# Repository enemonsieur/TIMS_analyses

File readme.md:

# TIMS Workspace Entry Point

This repository contains TIMS/TMS-EEG analysis code, experiment notes, and results across multiple experiments. This README is the navigation entry point for the workspace. It tells you where to start and where each kind of work lives. It is not the full scientific record.

## Workflow First

Use the repo in this order:

1. Read the latest memo chain to understand the current decision context.
2. Check the shared documentation files for memo, script, and figure rules.
3. Reuse the shared helper modules before adding logic to analysis scripts.
4. Open the main analyses when you need the scripts behind current conclusions.
5. Open exploratory analyses only when you are tracing probes, failed paths, or method tests.
6. Find outputs by experiment at the top level whenever possible.

## Latest Memo Chain

Memos in this repo are chained decision documents. Each new memo is expected to link the latest relevant earlier memo in its `Latest Shared Information` section, so the right reading order is newest to older, not oldest to newest. The current latest visible chain happens to be exp05, but that should not be assumed to stay true as the repo changes.

- Latest decision memo: [`MEMO_exp05_5_3_ctbs_intensity_decision.md`](/mnt/c/Users/njeuk/OneDrive/Documents/Charite%20Berlin/TIMS/docs/memos/MEMO_exp05_5_3_ctbs_intensity_decision.md)
- Immediate predecessor: [`MEMO_exp05_5_2_ctbs_recovery.md`](/mnt/c/Users/njeuk/OneDrive/Documents/Charite%20Berlin/TIMS/docs/memos/MEMO_exp05_5_2_ctbs_recovery.md)
- Earlier anchor in the same chain: [`MEMO_exp05_analysis.md`](/mnt/c/Users/njeuk/OneDrive/Documents/Charite%20Berlin/TIMS/docs/memos/MEMO_exp05_analysis.md)
- Memo rules/template: [`MEMO.md`](/mnt/c/Users/njeuk/OneDrive/Documents/Charite%20Berlin/TIMS/docs/memos/MEMO.md)

## How To Navigate TIMS

### Docs And Decision Records

- [`docs/memos/MEMO.md`](/mnt/c/Users/njeuk/OneDrive/Documents/Charite%20Berlin/TIMS/docs/memos/MEMO.md): memo template and chaining rules
- [`docs/standards/DATAVIZ_FRAMEWORK.md`](/mnt/c/Users/njeuk/OneDrive/Documents/Charite%20Berlin/TIMS/docs/standards/DATAVIZ_FRAMEWORK.md): figure planning and claim-first plotting rules
- [`docs/standards/SKRIPT.md`](/mnt/c/Users/njeuk/OneDrive/Documents/Charite%20Berlin/TIMS/docs/standards/SKRIPT.md): analysis script rules
- [`docs/standards/ANSWER.md`](/mnt/c/Users/njeuk/OneDrive/Documents/Charite%20Berlin/TIMS/docs/standards/ANSWER.md): response style guide for coding work
- [`docs/reference/TIMS_pilot_pipeline_map.md`](/mnt/c/Users/njeuk/OneDrive/Documents/Charite%20Berlin/TIMS/docs/reference/TIMS_pilot_pipeline_map.md): I/O-oriented pipeline map for the pilot/dose-response work
- [`docs/experiments/exp05.md`](/mnt/c/Users/njeuk/OneDrive/Documents/Charite%20Berlin/TIMS/docs/experiments/exp05.md): experiment-specific lab-book style reference for exp05

### Helper/Core Files

Shared reusable logic belongs in the core modules, not in new one-off scripts.

- [`preprocessing.py`](/mnt/c/Users/njeuk/OneDrive/Documents/Charite%20Berlin/TIMS/preprocessing.py): reusable preprocessing, epoching, timing, and metric helpers
- [`plot_helpers.py`](/mnt/c/Users/njeuk/OneDrive/Documents/Charite%20Berlin/TIMS/plot_helpers.py): reusable figure and plotting helpers

If logic is reused across analyses, it should be moved into one of these files instead of being copied into experiment scripts.

### Main Analyses

Main analyses are the scripts that support current conclusions or memo-backed outputs.

- [`main_analysis_exp03.py`](/mnt/c/Users/njeuk/OneDrive/Documents/Charite%20Berlin/TIMS/main_analysis_exp03.py)
- [`postclean_denoise_validate_exp03.py`](/mnt/c/Users/njeuk/OneDrive/Documents/Charite%20Berlin/TIMS/postclean_denoise_validate_exp03.py)
- [`compare_stim_baseline_exp03.py`](/mnt/c/Users/njeuk/OneDrive/Documents/Charite%20Berlin/TIMS/compare_stim_baseline_exp03.py)
- [`analyses_TEP_exp04.py`](/mnt/c/Users/njeuk/OneDrive/Documents/Charite%20Berlin/TIMS/analyses_TEP_exp04.py)
- [`analyses_spectral_exp04.py`](/mnt/c/Users/njeuk/OneDrive/Documents/Charite%20Berlin/TIMS/analyses_spectral_exp04.py)
- [`analyses_dynamics_exp04.py`](/mnt/c/Users/njeuk/OneDrive/Documents/Charite%20Berlin/TIMS/analyses_dynamics_exp04.py)
- [`analyses_artifact_exp05.py`](/mnt/c/Users/njeuk/OneDrive/Documents/Charite%20Berlin/TIMS/analyses_artifact_exp05.py)
- [`analyses_ssd_exp05.py`](/mnt/c/Users/njeuk/OneDrive/Documents/Charite%20Berlin/TIMS/analyses_ssd_exp05.py)

### Exploratory Analyses

Exploratory analyses are probes, method experiments, drafts, and non-decision-driving checks. They are useful for development and evidence, but they should not be treated as the default scientific entry point.

- [`analyses_ssd_exp05_skript.py`](/mnt/c/Users/njeuk/OneDrive/Documents/Charite%20Berlin/TIMS/analyses_ssd_exp05_skript.py)
- [`explore_exp05_fc1_baseline_ssd.py`](/mnt/c/Users/njeuk/OneDrive/Documents/Charite%20Berlin/TIMS/explore_exp05_fc1_baseline_ssd.py)
- [`analyses_ica_topo_exp05.py`](/mnt/c/Users/njeuk/OneDrive/Documents/Charite%20Berlin/TIMS/analyses_ica_topo_exp05.py)
- [`compare_baseline_gt_exp05.py`](/mnt/c/Users/njeuk/OneDrive/Documents/Charite%20Berlin/TIMS/compare_baseline_gt_exp05.py)
- [`analyze_baseline_gt.py`](/mnt/c/Users/njeuk/OneDrive/Documents/Charite%20Berlin/TIMS/analyze_baseline_gt.py)
- [`plot_channels_epoch_avg_exp05.py`](/mnt/c/Users/njeuk/OneDrive/Documents/Charite%20Berlin/TIMS/plot_channels_epoch_avg_exp05.py)
- [`evidence`](/mnt/c/Users/njeuk/OneDrive/Documents/Charite%20Berlin/TIMS/evidence): comparison runs, probes, and failure evidence
- [`old`](/mnt/c/Users/njeuk/OneDrive/Documents/Charite%20Berlin/TIMS/old): archived analyses and older experiment work

## Where Things Live

### Raw Data

- [`TIMS_data_sync`](/mnt/c/Users/njeuk/OneDrive/Documents/Charite%20Berlin/TIMS/TIMS_data_sync): BrainVision recordings and related synced data

### Protocol Files

- Top-level `.tims` and protocol `.py` files define programmable stimulation protocols used by specific experiments

### Main Results

Experiment outputs should be easy to find from the top level by experiment name.

- `exp03` outputs:
  - [`exp03_pulse_centered_analysis_run03`](/mnt/c/Users/njeuk/OneDrive/Documents/Charite%20Berlin/TIMS/exp03_pulse_centered_analysis_run03)
  - [`exp03_postpulse_fixed_channels`](/mnt/c/Users/njeuk/OneDrive/Documents/Charite%20Berlin/TIMS/exp03_postpulse_fixed_channels)
- `exp04` outputs:
  - [`EXP04_TEP_analysis`](/mnt/c/Users/njeuk/OneDrive/Documents/Charite%20Berlin/TIMS/EXP04_TEP_analysis)
  - [`EXP04_spectral_analysis`](/mnt/c/Users/njeuk/OneDrive/Documents/Charite%20Berlin/TIMS/EXP04_spectral_analysis)
  - [`EXP04_dynamics_analysis`](/mnt/c/Users/njeuk/OneDrive/Documents/Charite%20Berlin/TIMS/EXP04_dynamics_analysis)
- `exp05` outputs:
  - [`EXP05_artifact_characterization`](/mnt/c/Users/njeuk/OneDrive/Documents/Charite%20Berlin/TIMS/EXP05_artifact_characterization)
  - [`EXP05_baseline_gt_analysis`](/mnt/c/Users/njeuk/OneDrive/Documents/Charite%20Berlin/TIMS/EXP05_baseline_gt_analysis)
  - [`EXP05_baseline_comparison`](/mnt/c/Users/njeuk/OneDrive/Documents/Charite%20Berlin/TIMS/EXP05_baseline_comparison)
  - [`EXP05_channel_avg`](/mnt/c/Users/njeuk/OneDrive/Documents/Charite%20Berlin/TIMS/EXP05_channel_avg)
  - [`EXP05_explore_fc1_baseline_ssd`](/mnt/c/Users/njeuk/OneDrive/Documents/Charite%20Berlin/TIMS/EXP05_explore_fc1_baseline_ssd)
  - [`EXP05_ica_30pct`](/mnt/c/Users/njeuk/OneDrive/Documents/Charite%20Berlin/TIMS/EXP05_ica_30pct)
  - [`EXP05_ssd_recovery`](/mnt/c/Users/njeuk/OneDrive/Documents/Charite%20Berlin/TIMS/EXP05_ssd_recovery)
  - [`EXP05_ssd_recovery_skript`](/mnt/c/Users/njeuk/OneDrive/Documents/Charite%20Berlin/TIMS/EXP05_ssd_recovery_skript)
- `exp06` outputs:
  - [`EXP06_qc_context`](/mnt/c/Users/njeuk/OneDrive/Documents/Charite%20Berlin/TIMS/EXP06_qc_context)

### Exploratory Or Legacy Results

- [`evidence`](/mnt/c/Users/njeuk/OneDrive/Documents/Charite%20Berlin/TIMS/evidence): probe outputs and comparison artifacts
- [`old`](/mnt/c/Users/njeuk/OneDrive/Documents/Charite%20Berlin/TIMS/old): archived or legacy material that is no longer in the active result layout

## Classification Rules

- Main analyses: scripts that directly support current conclusions, memo-backed figures, or decision documents
- Exploratory analyses: probes, method tests, drafts, and diagnostics that help development but are not the default basis for conclusions
- Results: organize by experiment at the top level where possible, and avoid deep nested result trees unless there is a clear need

## Current Layout Issues

The repo now uses top-level experiment result folders more consistently, but there are still cleanup edges to resolve over time. The remaining direction is to keep new outputs experiment-scoped at the top level, avoid loose result files in the repo root, and keep exploratory material clearly separated from main result folders.

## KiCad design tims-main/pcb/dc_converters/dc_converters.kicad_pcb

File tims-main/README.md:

# tims
Design files for a Temporal Interference Magnetic Stimulator (TIMS)

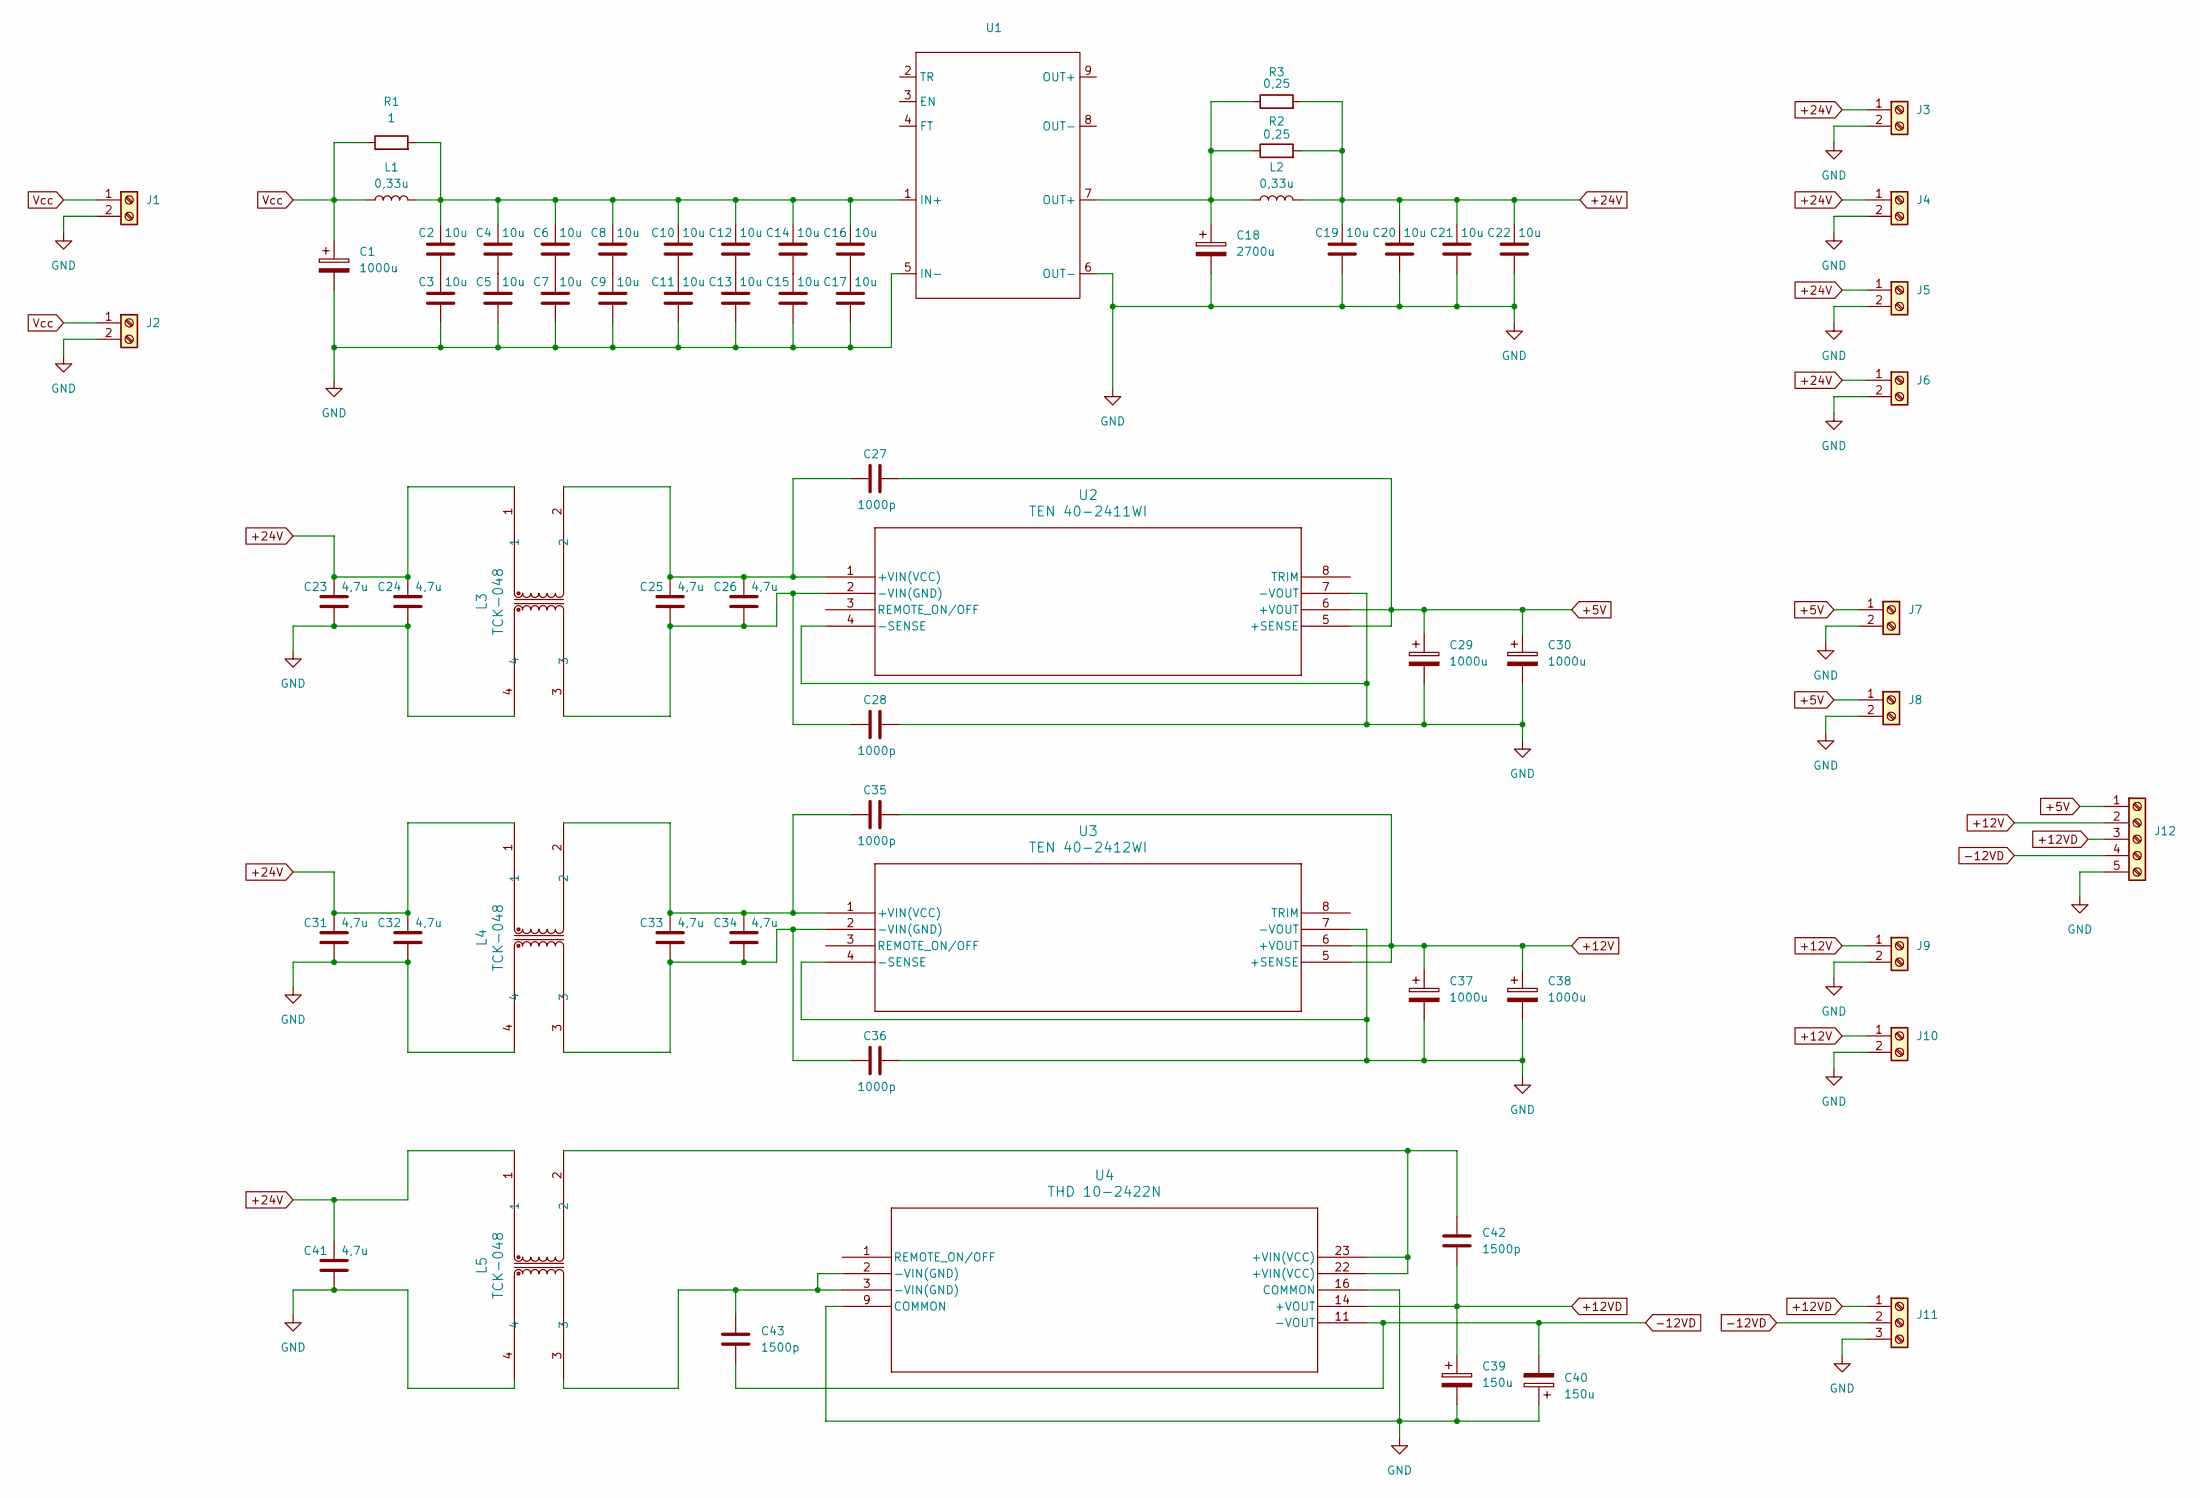
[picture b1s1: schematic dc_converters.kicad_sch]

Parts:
C1: 1000u; CP_Radial_D30.0mm_P10.00mm_SnapIn
C2, C3, C4, C5, C6, C7, C8, C9, C10, C11, C12, C13, C14, C15, C16, C17, C19, C20, C21, C22: 10u; C_1210_3225Metric
C18: 2700u; CP_Radial_D18.0mm_P7.50mm
C23, C24, C25, C26, C31, C32, C33, C34, C41: 4,7u; C_1206_3216Metric
C27, C28, C35, C36: 1000p; C_1206_3216Metric
C29, C30, C37, C38: 1000u; CP_Radial_D12.5mm_P5.00mm
C39, C40: 150u; CP_Radial_D10.0mm_P5.00mm
C42, C43: 1500p; C_1206_3216Metric
J1, J2, J3, J4, J5, J6, J7, J8, J9, J10: TerminalBlock_Phoenix_PT-1,5-2-5.0-H_1x02_P5.00mm_Horizontal
J11: TerminalBlock_Phoenix_PT-1,5-3-5.0-H_1x03_P5.00mm_Horizontal
J12: TerminalBlock_Phoenix_PT-1,5-5-5.0-H_1x05_P5.00mm_Horizontal
L1, L2: 0,33u; L_Wuerth_HCM-1390
L3, L4, L5: TCK-048; IND_TCK-048_TRP
R1: 1; R_1206_3216Metric
R2, R3: 0,25; R_2512_6332Metric
U1: DCM3623TA5N26B4T00
U2: TEN 40-2411WI; TEN 40WI_TRP
U3: TEN 40-2412WI; TEN 40WI_TRP
U4: THD 10-2422N; THD 10N DUAL_TRP

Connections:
+5V: C27.2, C29.1, C30.1, J7.1, J8.1, J12.1, U2.5 (+SENSE), U2.6 (+VOUT)
+12V: C35.2, C37.1, C38.1, J9.1, J10.1, J12.2, U3.5 (+SENSE), U3.6 (+VOUT)
+12VD: C39.1, C42.2, J11.1, J12.3, U4.14 (+VOUT)
+24V: C19.1, C20.1, C21.1, C22.1, C23.1, C24.1, C31.1, C32.1, C41.1, J3.1, J4.1, J5.1, J6.1, L2.2, L3.1, L4.1, L5.1, R2.2, R3.2
-12VD: C40.2, C43.2, J11.2, J12.4, U4.11 (-VOUT)
GND: C1.2, C3.2, C5.2, C7.2, C9.2, C11.2, C13.2, C15.2, C17.2, C18.2, C19.2, C20.2, C21.2, C22.2, C23.2, C24.2, C28.2, C29.2, C30.2, C31.2, C32.2, C36.2, C37.2, C38.2, C39.2, C40.1, C41.2, J1.2, J2.2, J3.2, J4.2, J5.2, J6.2, J7.2, J8.2, J9.2, J10.2, J11.3, J12.5, L3.4, L4.4, L5.4, U1.5 (IN-), U1.6 (OUT-), U2.4 (-SENSE), U2.7 (-VOUT), U3.4 (-SENSE), U3.7 (-VOUT), U4.9 (COMMON), U4.16 (COMMON)
unnamed: C2.2, C3.1
unnamed: C4.2, C5.1
unnamed: C6.2, C7.1
unnamed: C8.2, C9.1
unnamed: C10.2, C11.1
unnamed: C12.2, C13.1
unnamed: C14.2, C15.1
unnamed: C16.2, C17.1
unnamed: C18.1, L2.1, R2.1, R3.1, U1.7 (OUT+)
unnamed: C42.1, L5.2, U4.22 (+VIN(VCC)), U4.23 (+VIN(VCC))
unnamed: C43.1, L5.3, U4.2 (-VIN(GND)), U4.3 (-VIN(GND))
unnamed: C2.1, C4.1, C6.1, C8.1, C10.1, C12.1, C14.1, C16.1, L1.2, R1.2, U1.1 (IN+)
unnamed: C25.1, C26.1, C27.1, L3.2, U2.1 (+VIN(VCC))
unnamed: C25.2, C26.2, C28.1, L3.3, U2.2 (-VIN(GND))
unnamed: C33.1, C34.1, C35.1, L4.2, U3.1 (+VIN(VCC))
unnamed: C33.2, C34.2, C36.1, L4.3, U3.2 (-VIN(GND))
Vcc: C1.1, J1.1, J2.1, L1.1, R1.1

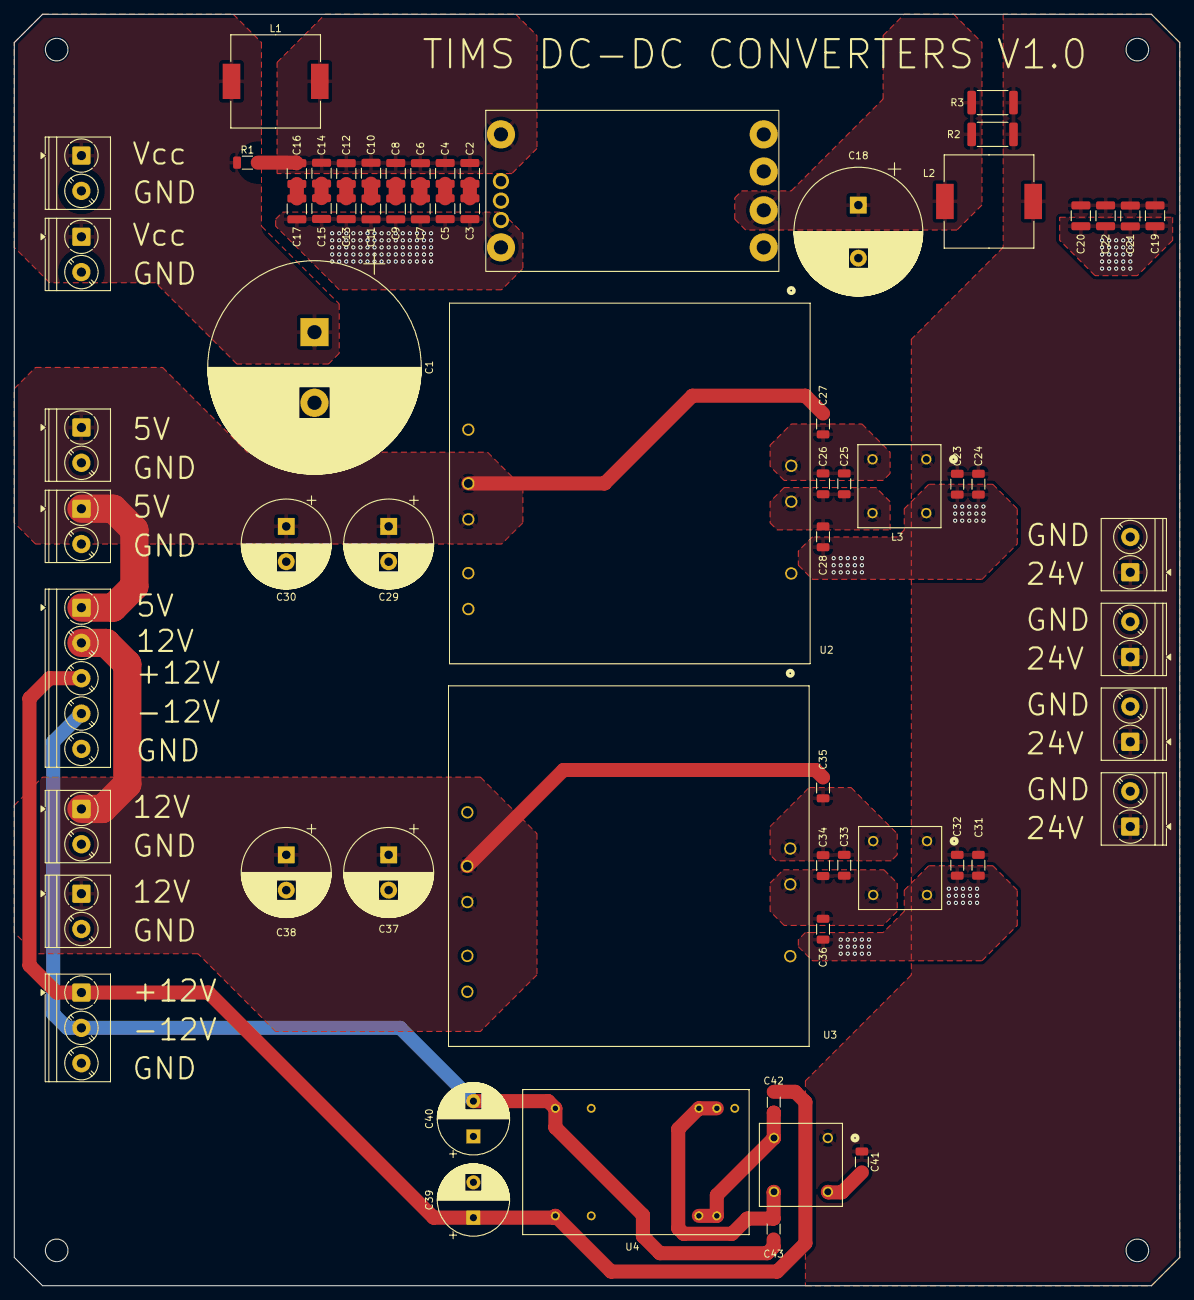
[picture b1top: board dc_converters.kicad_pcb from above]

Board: 2 copper layers, 165.0 x 180.0 mm, 67 parts (0 on the bottom side), 23 nets.

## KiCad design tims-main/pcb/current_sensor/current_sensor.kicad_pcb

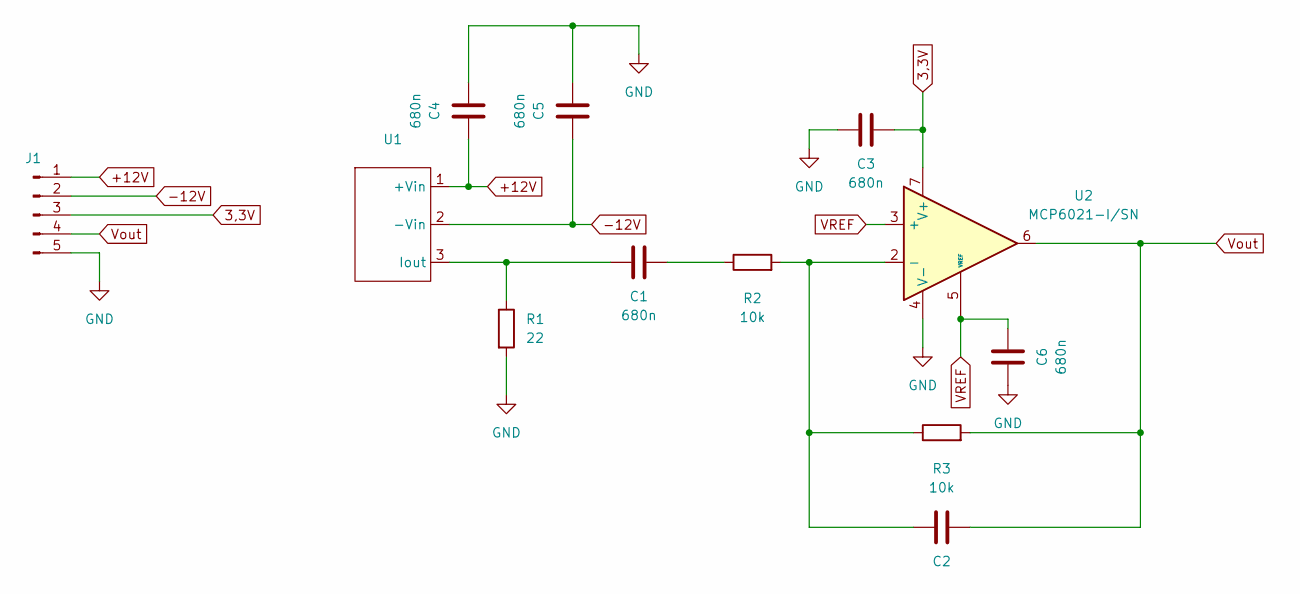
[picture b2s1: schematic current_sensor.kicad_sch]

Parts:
C1, C3, C4, C5, C6: 680n; C_1206_3216Metric
C2: C_1206_3216Metric
J1: Conn_01x05_Pin; JST_PH_B5B-PH-K_1x05_P2.00mm_Vertical
R1: 22; R_1206_3216Metric
R2, R3: 10k; R_1206_3216Metric
U1: CSNT651
U2: MCP6021-I/SN; SOIC-8_3.9x4.9mm_P1.27mm

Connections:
3,3V: C3.1, J1.3, U2.7 (V+)
+12V: C4.1, J1.1, U1.1 (+Vin)
-12V: C5.1, J1.2, U1.2 (-Vin)
GND: C3.2, C4.2, C5.2, C6.2, J1.5, R1.2, U2.4 (V-)
unnamed: C1.1, R2.1
unnamed: C1.2, R1.1, U1.3 (Iout)
unnamed: C2.2, R2.2, R3.1, U2.2 (-)
VREF: C6.1, U2.3 (+), U2.5 (VREF)
Vout: C2.1, J1.4, R3.2, U2.6

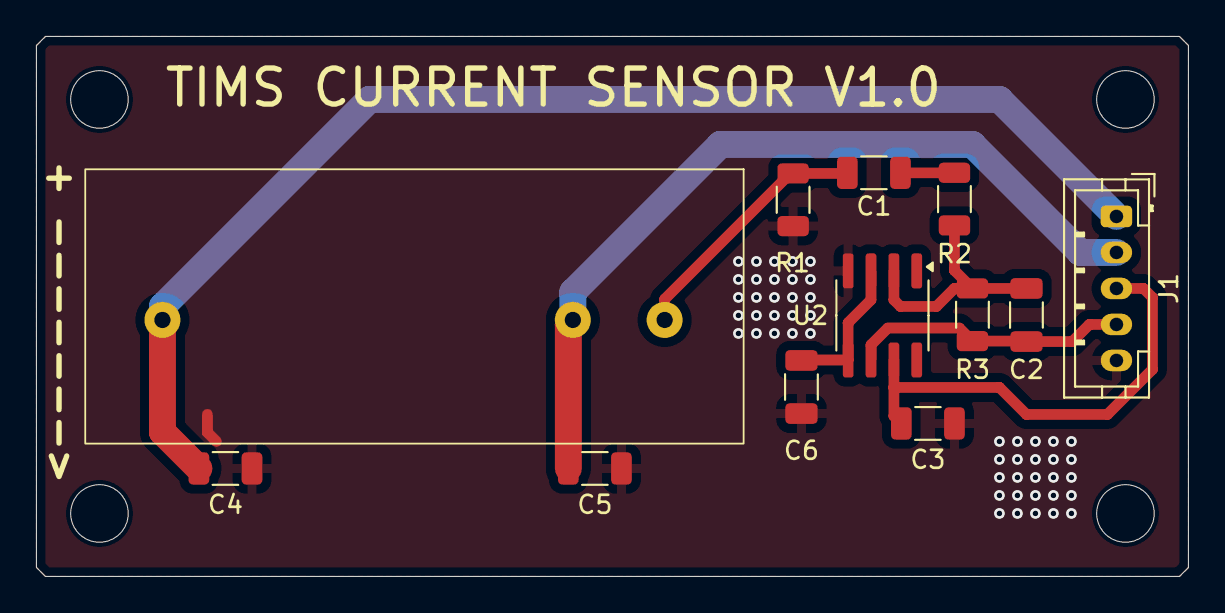
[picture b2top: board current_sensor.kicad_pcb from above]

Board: 2 copper layers, 64.0 x 30.0 mm, 12 parts (0 on the bottom side), 9 nets.

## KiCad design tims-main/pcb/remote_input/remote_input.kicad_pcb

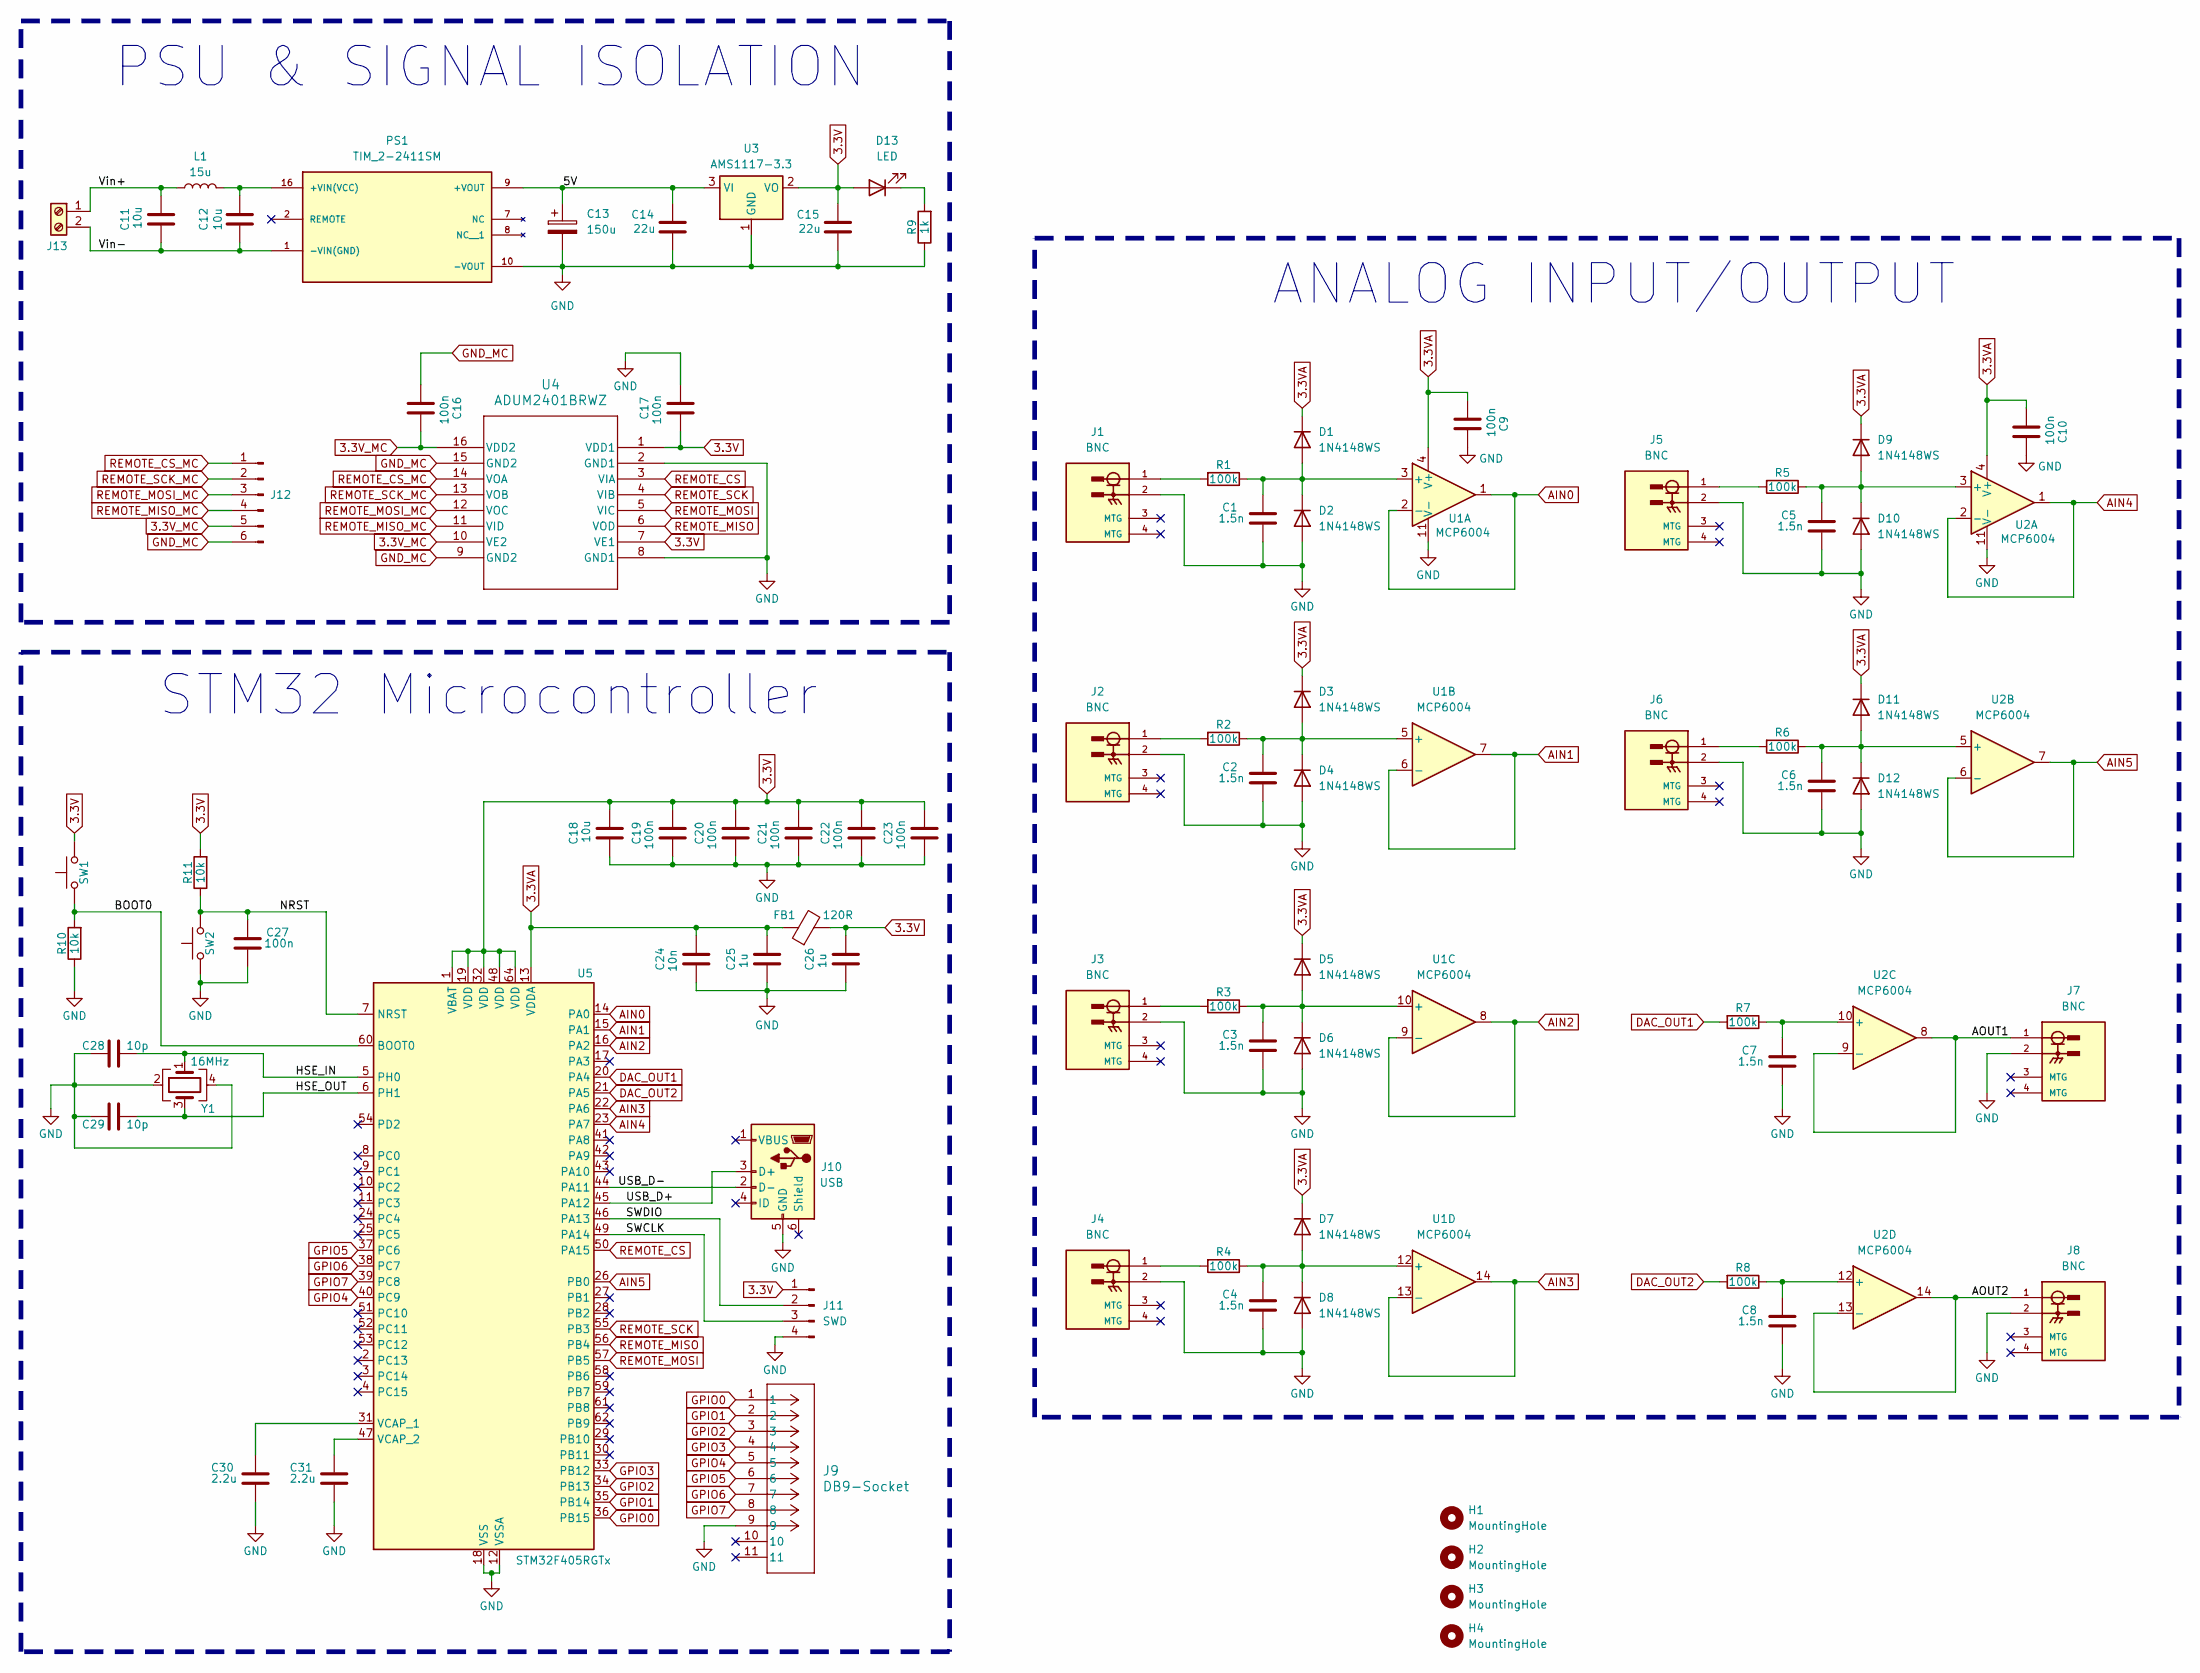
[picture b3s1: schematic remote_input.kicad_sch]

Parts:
C1, C2, C3, C4, C5, C6, C7, C8: 1.5n; C_1206_3216Metric
C9, C10, C16, C17, C19, C20, C21, C22, C23, C27: 100n; C_0402_1005Metric
C11, C12: 10u; C_1206_3216Metric
C13: 150u; CP_Radial_D10.0mm_P5.00mm
C14, C15: 22u; C_0805_2012Metric
C18: 10u; C_0603_1608Metric
C24: 10n; C_0402_1005Metric
C25, C26: 1u; C_0603_1608Metric
C28, C29: 10p; C_0402_1005Metric
C30, C31: 2.2u; C_0603_1608Metric
D1, D2, D3, D4, D5, D6, D7, D8, D9, D10, D11, D12: 1N4148WS; D_SOD-323
D13: LED; LED_0805_2012Metric
FB1: 120R; L_1206_3216Metric
H1, H2, H3, H4: MountingHole; MountingHole_3.2mm_M3
J1, J2, J3, J4, J5, J6, J7, J8: BNC; BNC-5227161-1; PARTREV B4
J9: DB9-Socket; DB9_SOCKET_2311765_TEC
J10: USB; USB_Micro-B_Wuerth_629105150521_WITH_3D
J11: SWD; PinHeader_1x04_P2.54mm_Vertical
J12: Conn_01x06_Pin; JST_PH_B6B-PH-K_1x06_P2.00mm_Vertical
J13: TerminalBlock_Phoenix_PT-1,5-2-5.0-H_1x02_P5.00mm_Horizontal
L1: 15u; IND_K-131_TRP
PS1: TIM_2-2411SM; CONV_TIM_2-2411SM; PARTREV August 20, 2020
R1, R2, R3, R4, R5, R6, R7, R8: 100k; R_1206_3216Metric
R9: 1k; R_1206_3216Metric
R10, R11: 10k; R_1206_3216Metric
SW1, SW2: SW_Push; SW-TS-1088-AR02016
U1, U2: MCP6004; SOIC-14_3.9x8.7mm_P1.27mm
U3: AMS1117-3.3; SOT-223-3_TabPin2
U4: ADUM2401BRWZ; SOIC-16W_7.5x10.3mm_P1.27mm
U5: STM32F405RGTx; LQFP-64_10x10mm_P0.5mm
Y1: 16MHz; Crystal_SMD_3225-4Pin_3.2x2.5mm

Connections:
3.3V: C15.2, C17.1, C18.1, C19.2, C20.2, C21.2, C22.2, C23.2, C26.2, D13.2 (A), FB1.2, J11.1, R11.2, SW1.2, U3.2 (VO), U4.1 (VDD1), U4.7 (VE1), U5.1 (VBAT), U5.19 (VDD), U5.32 (VDD), U5.48 (VDD), U5.64 (VDD)
3.3VA: C9.1, C10.1, C24.2, C25.2, D1.1 (K), D3.1 (K), D5.1 (K), D7.1 (K), D9.1 (K), D11.1 (K), FB1.1, U1.4 (V+), U2.4 (V+), U5.13 (VDDA)
3.3V_MC: C16.1, J12.5, U4.10 (VE2), U4.16 (VDD2)
/5V: C13.1, C14.2, PS1.9 (+VOUT), U3.3 (VI)
/AOUT1: J7.1, U2.8, U2.9 (-)
/AOUT2: J8.1, U2.13 (-), U2.14
/BOOT0: R10.2, SW1.1, U5.60 (BOOT0)
/HSE_IN: C28.1, U5.5 (PH0), Y1.1
/HSE_OUT: C29.1, U5.6 (PH1), Y1.3
/NRST: C27.2, R11.1, SW2.2, U5.7 (NRST)
/SWCLK: J11.3, U5.49 (PA14)
/SWDIO: J11.2, U5.46 (PA13)
/USB_D+: J10.3 (D+), U5.45 (PA12)
/USB_D-: J10.2 (D-), U5.44 (PA11)
/Vin+: C11.1, J13.1, L1.1
/Vin-: C11.2, C12.2, J13.2, PS1.1 (-VIN(GND))
AIN0: U1.1, U1.2 (-), U5.14 (PA0)
AIN1: U1.6 (-), U1.7, U5.15 (PA1)
AIN2: U1.8, U1.9 (-), U5.16 (PA2)
AIN3: U1.13 (-), U1.14, U5.22 (PA6)
AIN4: U2.1, U2.2 (-), U5.23 (PA7)
AIN5: U2.6 (-), U2.7, U5.26 (PB0)
DAC_OUT1: R7.2, U5.20 (PA4)
DAC_OUT2: R8.2, U5.21 (PA5)
GND: C1.1, C2.1, C3.1, C4.1, C5.1, C6.1, C7.1, C8.1, C9.2, C10.2, C13.2, C14.1, C15.1, C17.2, C18.2, C19.1, C20.1, C21.1, C22.1, C23.1, C24.1, C25.1, C26.1, C27.1, C28.2, C29.2, C30.1, C31.1, D2.2 (A), D4.2 (A), D6.2 (A), D8.2 (A), D10.2 (A), D12.2 (A), J1.2, J2.2, J3.2, J4.2, J5.2, J6.2, J7.2, J8.2, J9.9, J10.5 (GND), J11.4, PS1.10 (-VOUT), R9.1, R10.1, SW2.1, U1.11 (V-), U2.11 (V-), U3.1 (GND), U4.2 (GND1), U4.8 (GND1), U5.12 (VSSA), U5.18 (VSS), U5.63 (VSS), Y1.2, Y1.4
GND_MC: C16.2, J12.6, U4.9 (GND2), U4.15 (GND2)
GPIO0: J9.1, U5.36 (PB15)
GPIO1: J9.2, U5.35 (PB14)
GPIO2: J9.3, U5.34 (PB13)
GPIO3: J9.4, U5.33 (PB12)
GPIO4: J9.5, U5.40 (PC9)
GPIO5: J9.6, U5.37 (PC6)
GPIO6: J9.7, U5.38 (PC7)
GPIO7: J9.8, U5.39 (PC8)
unnamed: C1.2, D1.2 (A), D2.1 (K), R1.1, U1.3 (+)
unnamed: C2.2, D3.2 (A), D4.1 (K), R2.1, U1.5 (+)
unnamed: C3.2, D5.2 (A), D6.1 (K), R3.1, U1.10 (+)
unnamed: C4.2, D7.2 (A), D8.1 (K), R4.1, U1.12 (+)
unnamed: C5.2, D9.2 (A), D10.1 (K), R5.1, U2.3 (+)
unnamed: C6.2, D11.2 (A), D12.1 (K), R6.1, U2.5 (+)
unnamed: D13.1 (K), R9.2
unnamed: J1.1, R1.2
unnamed: J2.1, R2.2
unnamed: J3.1, R3.2
unnamed: J4.1, R4.2
unnamed: J5.1, R5.2
unnamed: J6.1, R6.2
unnamed: C12.1, L1.2, PS1.16 (+VIN(VCC))
unnamed: C7.2, R7.1, U2.10 (+)
unnamed: C8.2, R8.1, U2.12 (+)
unnamed: C30.2, U5.31 (VCAP_1)
unnamed: C31.2, U5.47 (VCAP_2)
REMOTE_CS: U4.3 (VIA), U5.50 (PA15)
REMOTE_CS_MC: J12.1, U4.14 (VOA)
REMOTE_MISO: U4.6 (VOD), U5.56 (PB4)
REMOTE_MISO_MC: J12.4, U4.11 (VID)
REMOTE_MOSI: U4.5 (VIC), U5.57 (PB5)
REMOTE_MOSI_MC: J12.3, U4.12 (VOC)
REMOTE_SCK: U4.4 (VIB), U5.55 (PB3)
REMOTE_SCK_MC: J12.2, U4.13 (VOB)

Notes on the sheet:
PSU & SIGNAL ISOLATION
STM32 Microcontroller
ANALOG INPUT/OUTPUT

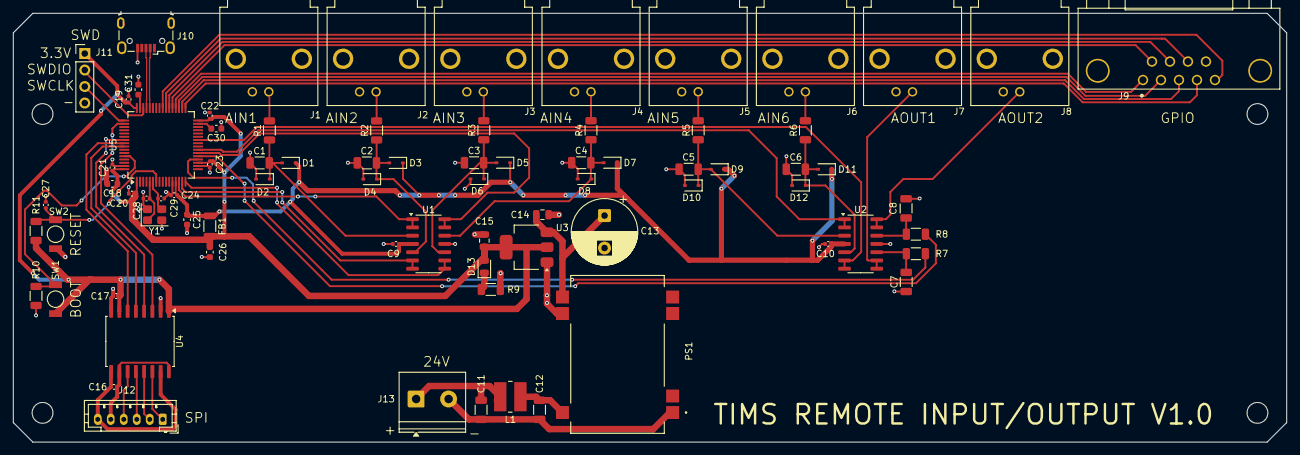
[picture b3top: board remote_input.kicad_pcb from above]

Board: 2 copper layers, 196.0 x 66.0 mm, 83 parts (0 on the bottom side), 60 nets.

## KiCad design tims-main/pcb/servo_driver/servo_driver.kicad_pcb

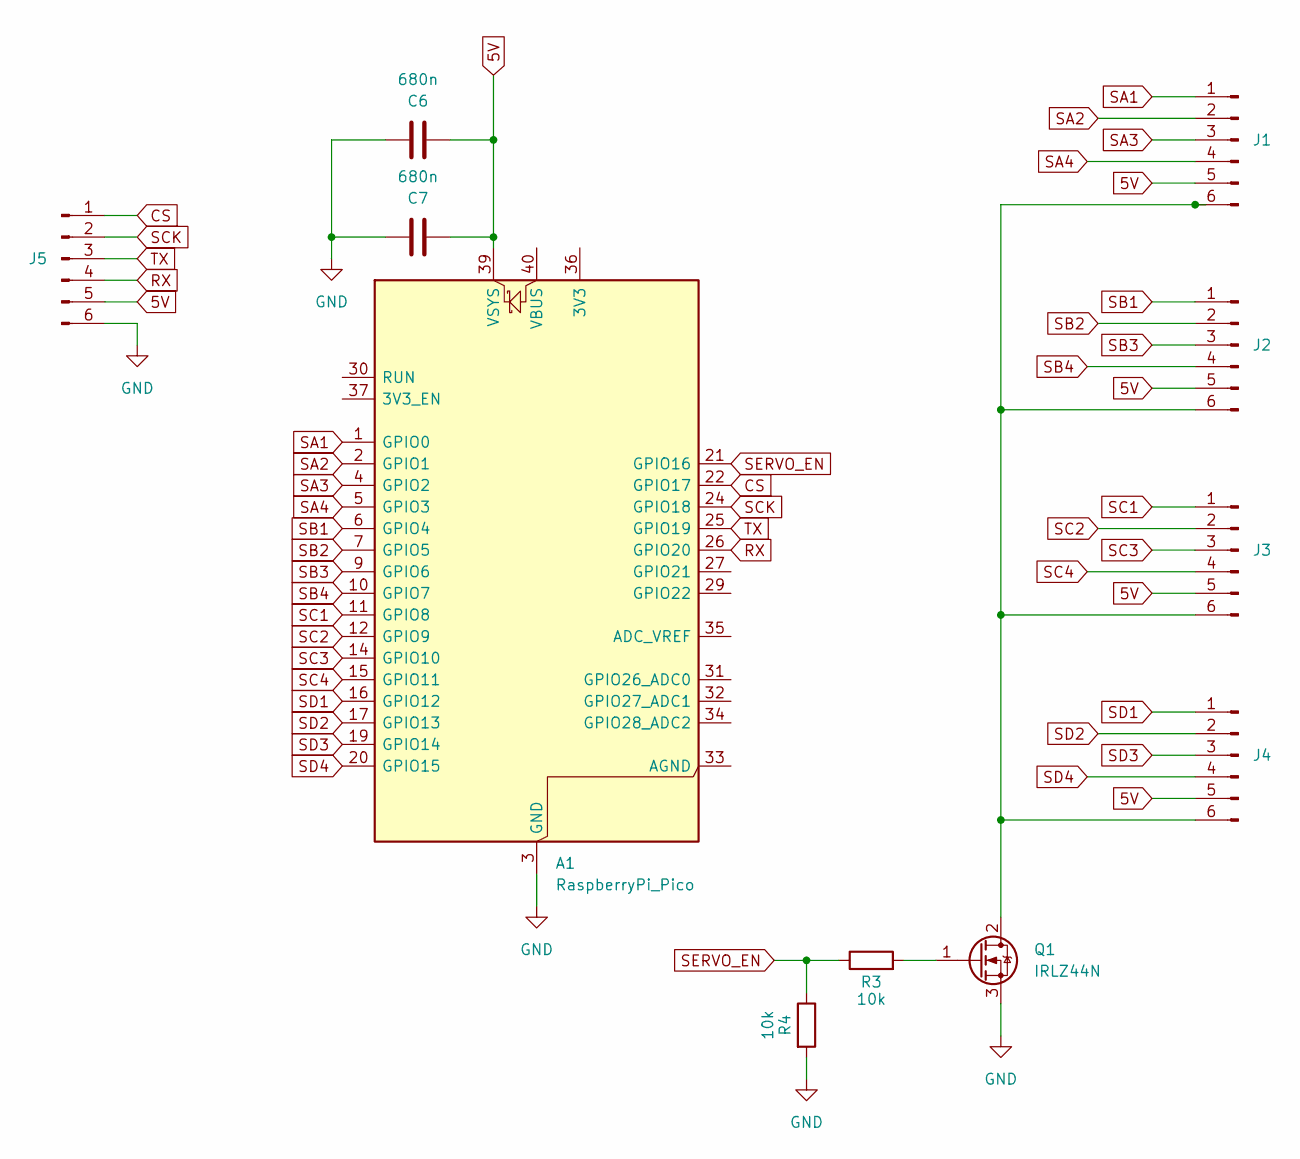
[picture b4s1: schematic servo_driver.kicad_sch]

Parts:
A1: RaspberryPi_Pico; RaspberryPi_Pico_Common_Unspecified
C6, C7: 680n; C_1206_3216Metric
J1, J2, J3, J4, J5: Conn_01x06_Pin; JST_PH_B6B-PH-K_1x06_P2.00mm_Vertical
Q1: IRLZ44N; TO-220-3_Vertical
R3, R4: 10k; R_1206_3216Metric

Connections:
5V: A1.39 (VSYS), C6.2, C7.2, J1.5, J2.5, J3.5, J4.5, J5.5
CS: A1.22 (GPIO17), J5.1
GND: A1.3 (GND), A1.8 (GND), A1.13 (GND), A1.18 (GND), A1.23 (GND), A1.28 (GND), A1.38 (GND), C6.1, C7.1, J5.6, Q1.3 (S), R4.2
unnamed: J1.6, J2.6, J3.6, J4.6, Q1.2 (D)
unnamed: Q1.1 (G), R3.2
RX: A1.26 (GPIO20), J5.4
SA1: A1.1 (GPIO0), J1.1
SA2: A1.2 (GPIO1), J1.2
SA3: A1.4 (GPIO2), J1.3
SA4: A1.5 (GPIO3), J1.4
SB1: A1.6 (GPIO4), J2.1
SB2: A1.7 (GPIO5), J2.2
SB3: A1.9 (GPIO6), J2.3
SB4: A1.10 (GPIO7), J2.4
SC1: A1.11 (GPIO8), J3.1
SC2: A1.12 (GPIO9), J3.2
SC3: A1.14 (GPIO10), J3.3
SC4: A1.15 (GPIO11), J3.4
SCK: A1.24 (GPIO18), J5.2
SD1: A1.16 (GPIO12), J4.1
SD2: A1.17 (GPIO13), J4.2
SD3: A1.19 (GPIO14), J4.3
SD4: A1.20 (GPIO15), J4.4
SERVO_EN: A1.21 (GPIO16), R3.1, R4.1
TX: A1.25 (GPIO19), J5.3

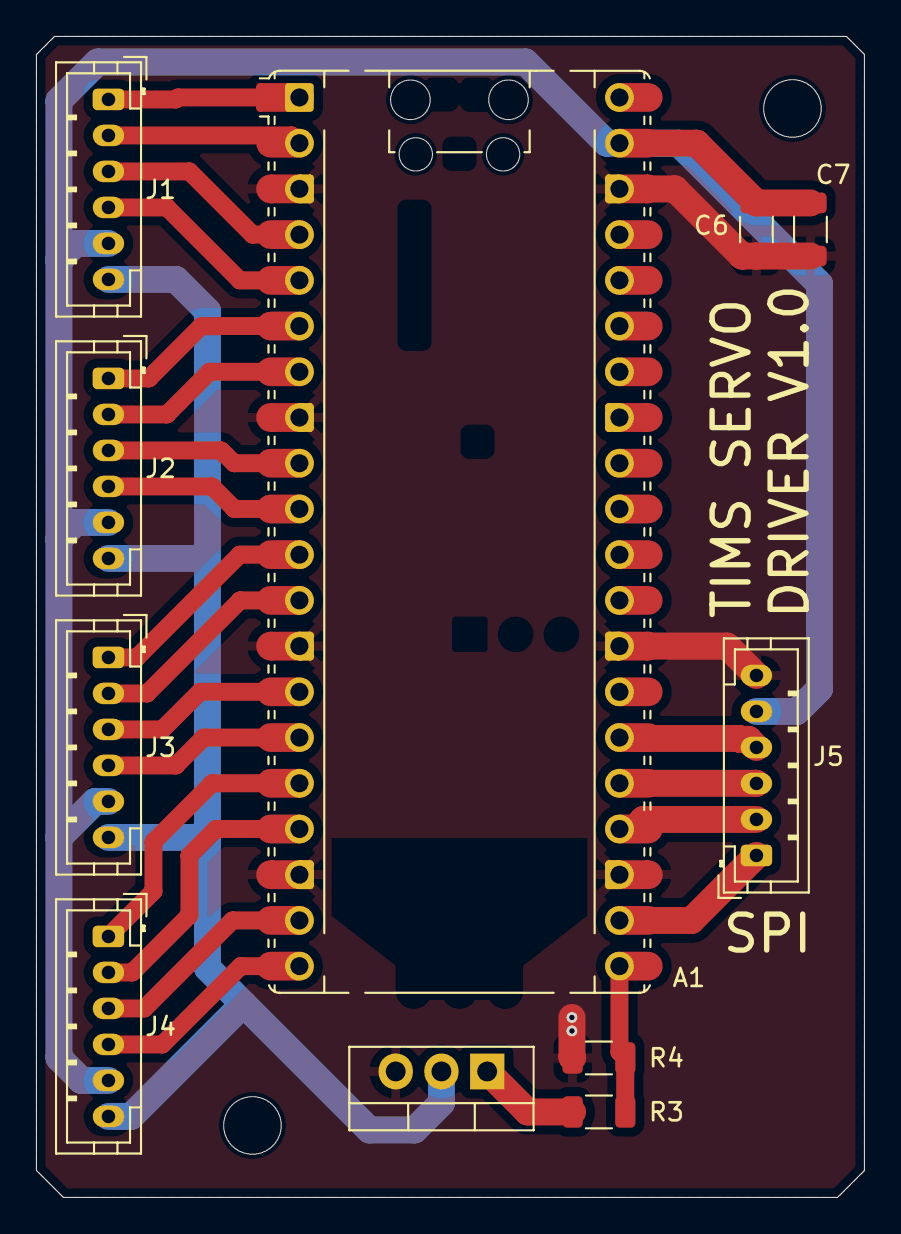
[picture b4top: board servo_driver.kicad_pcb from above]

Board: 2 copper layers, 46.0 x 64.5 mm, 11 parts (0 on the bottom side), 25 nets.

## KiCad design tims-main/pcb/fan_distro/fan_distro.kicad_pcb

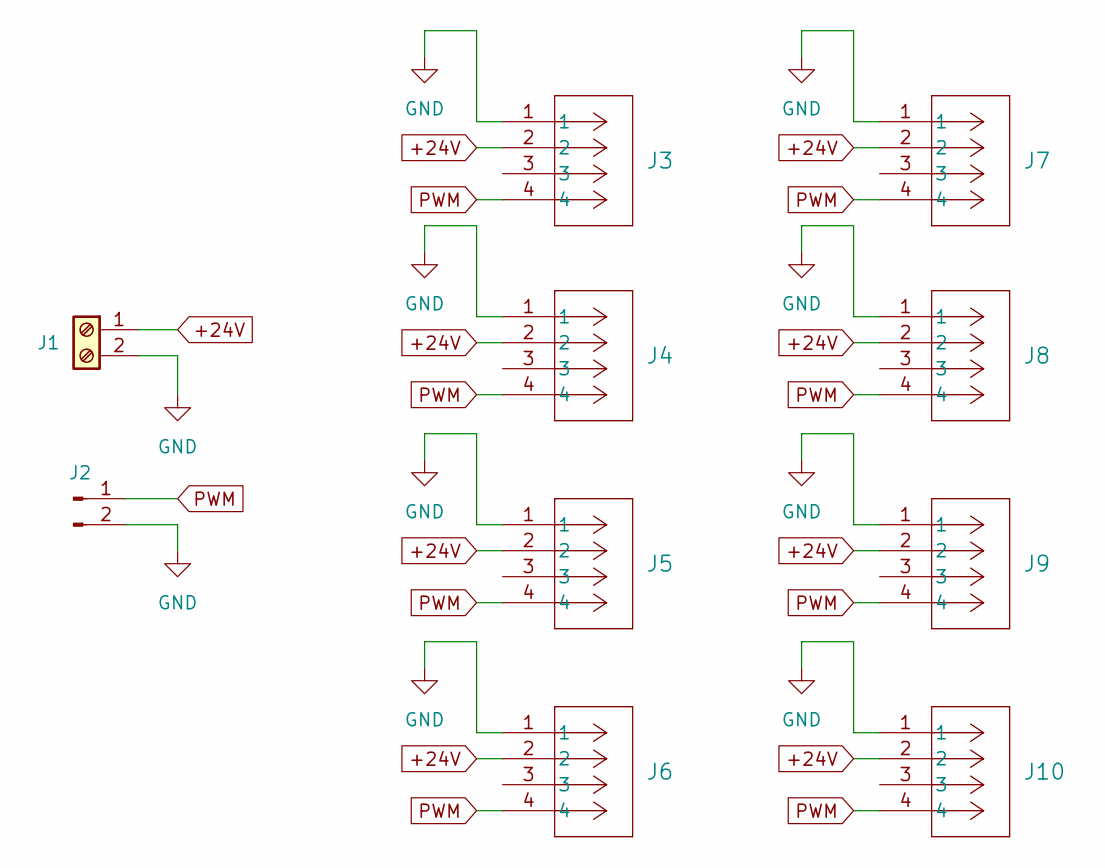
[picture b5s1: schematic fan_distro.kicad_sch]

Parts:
J1: Screw_Terminal_01x02; TerminalBlock_Phoenix_PT-1,5-2-5.0-H_1x02_P5.00mm_Horizontal
J2: Conn_01x02_Pin; JST_PH_B2B-PH-K_1x02_P2.00mm_Vertical
J3, J4, J5, J6, J7, J8, J9, J10: Molex 470531000; CONN_SD-47053-001_H10p00_MOL

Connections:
+24V: J1.1, J3.2, J4.2, J5.2, J6.2, J7.2, J8.2, J9.2, J10.2
GND: J1.2, J2.2, J3.1, J4.1, J5.1, J6.1, J7.1, J8.1, J9.1, J10.1
PWM: J2.1, J3.4, J4.4, J5.4, J6.4, J7.4, J8.4, J9.4, J10.4
